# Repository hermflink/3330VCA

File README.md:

# 3330VCA

Kicad project files of a AS3330 based dual VCA. Part of a modular DIY synth project, other modules are available in other repositories. Not entirely compatible with a CEM3330 as this would require a diode to ground on pin 4.

Used the Audio.lib from https://kicad.github.io/symbols/Audio to extend the Kicad library for the AS3330 component.

Designed to work with +/- 15V, not tested for +/- 12V

The PCB is 9.5 x 5.5 cm and has no PCB-mounting of potmeters, switches, jacks; these are all connected by pin header connectors

The PCB  has a fault: the connection between pin 5 and 8 of AS3330 on the backplane should be removed. Instead, pin 5 should be connected to R15/R17 as the schema points out.

Loosely based on http://www.digisound80.co.uk/digisound/modules/80-9_files/80-9_ETI.pdf

R4, C2, R18 and C8 can be safely left out.

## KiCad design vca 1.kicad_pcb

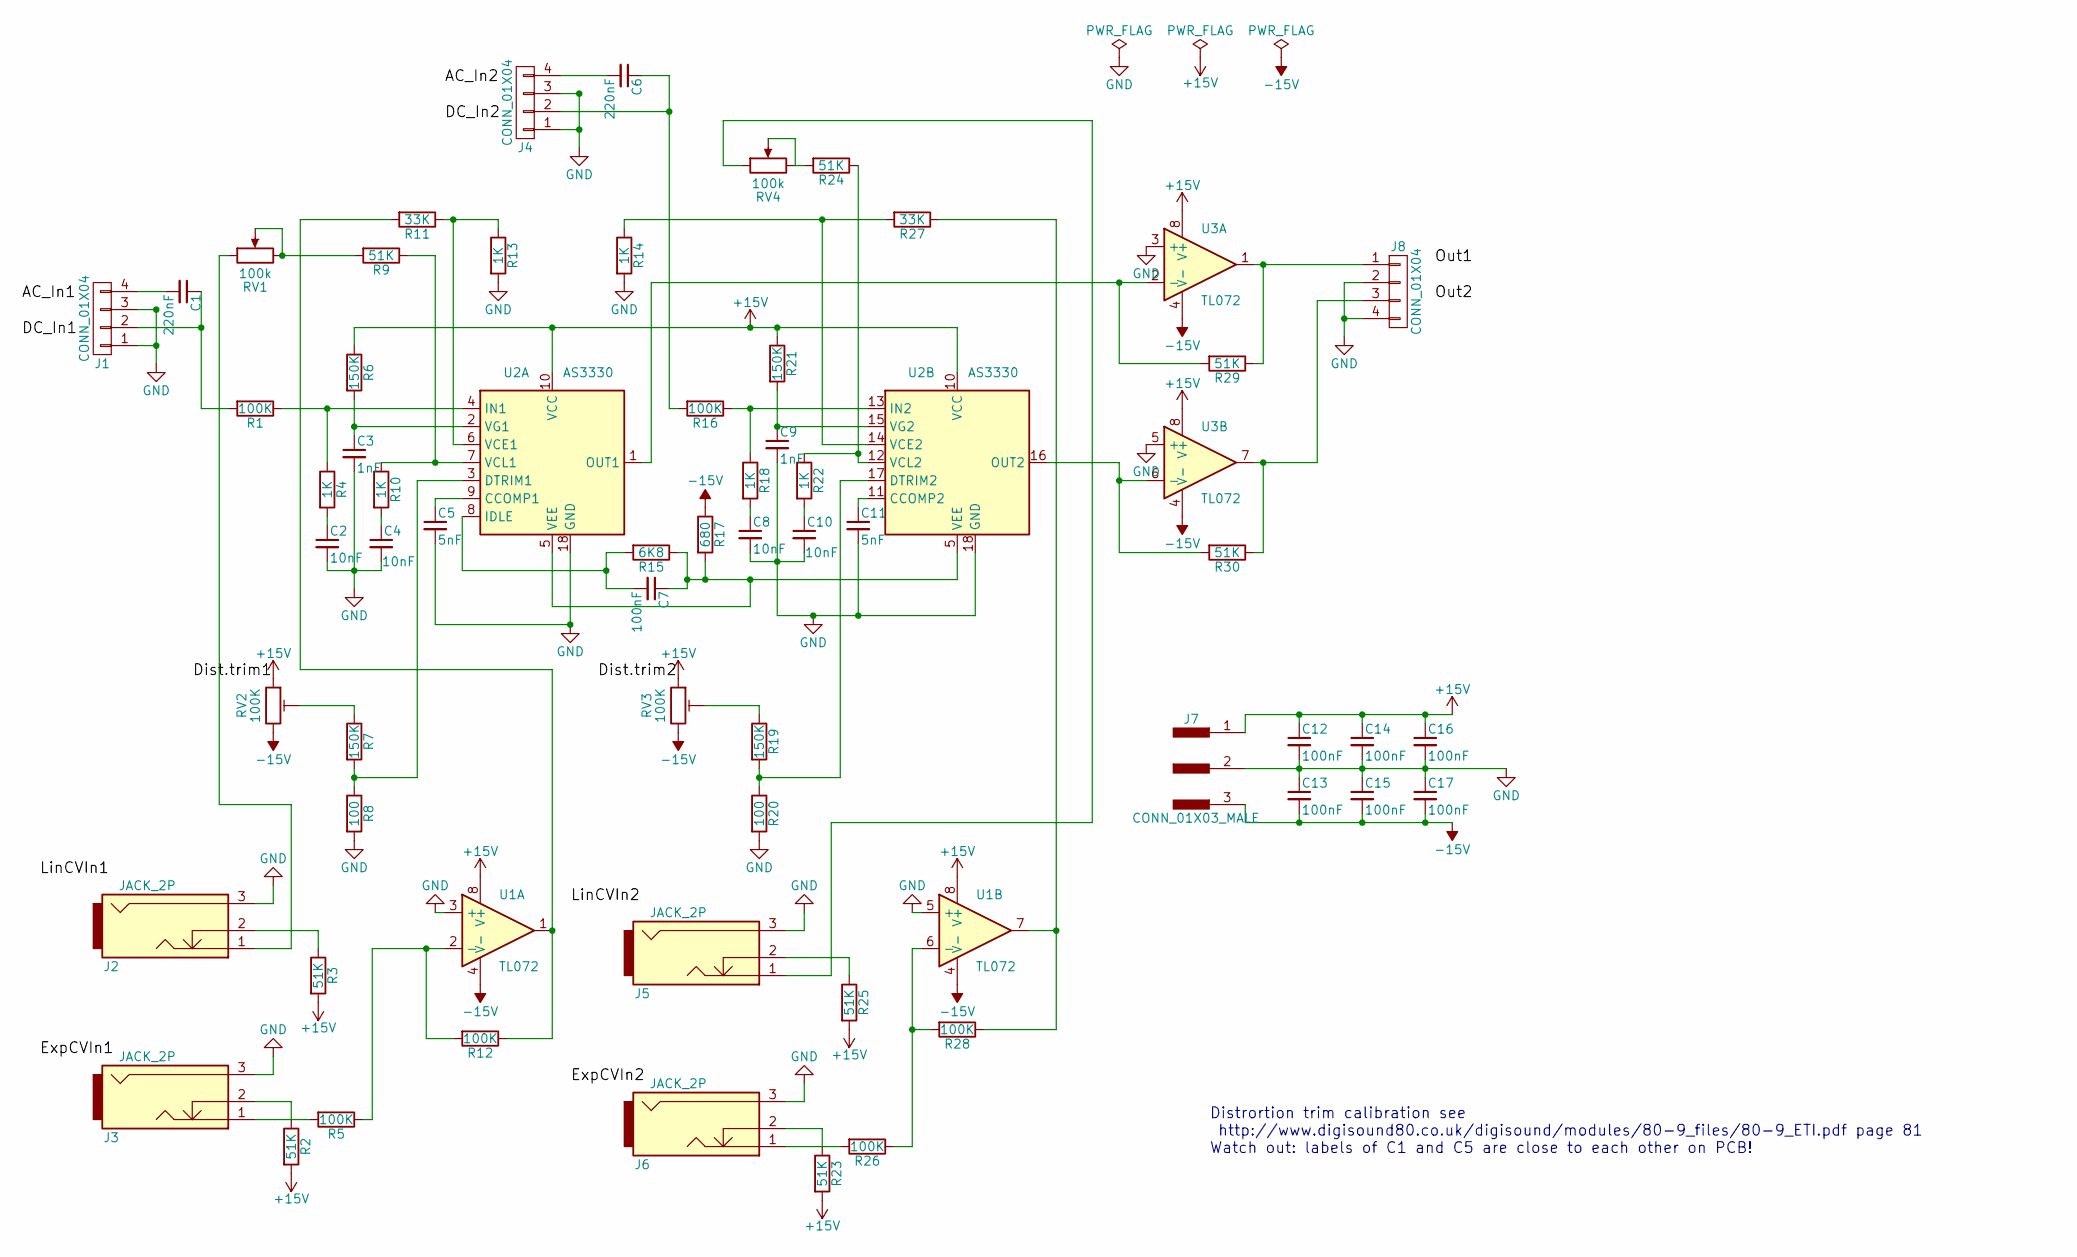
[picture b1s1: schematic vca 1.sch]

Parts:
C1, C6: 220nF; C_Disc_D5.0mm_W2.5mm_P5.00mm
C2, C4, C8, C10: 10nF; C_Disc_D5.0mm_W2.5mm_P5.00mm
C3, C9: 1nF; C_Disc_D5.0mm_W2.5mm_P5.00mm
C5, C11: 5nF; C_Disc_D5.0mm_W2.5mm_P5.00mm
C7, C12, C13, C14, C15, C16, C17: 100nF; C_Disc_D5.0mm_W2.5mm_P5.00mm
J1, J4, J8: CONN_01X04; Pin_Header_Straight_1x04_Pitch2.54mm
J2, J3, J5, J6: JACK_2P; Pin_Header_Straight_1x03_Pitch2.54mm
J7: CONN_01X03_MALE; Pin_Header_Straight_1x03_Pitch2.54mm
R1, R5, R12, R16, R26, R28: 100K; R_Axial_DIN0207_L6.3mm_D2.5mm_P2.54mm_Vertical
R2, R3, R9, R23, R24, R25, R29, R30: 51K; R_Axial_DIN0207_L6.3mm_D2.5mm_P2.54mm_Vertical
R4, R10, R13, R14, R18, R22: 1K; R_Axial_DIN0207_L6.3mm_D2.5mm_P2.54mm_Vertical
R6, R7, R19, R21: 150K; R_Axial_DIN0207_L6.3mm_D2.5mm_P2.54mm_Vertical
R8, R20: 100; R_Axial_DIN0207_L6.3mm_D2.5mm_P2.54mm_Vertical
R11, R27: 33K; R_Axial_DIN0207_L6.3mm_D2.5mm_P2.54mm_Vertical
R15: 6K8; R_Axial_DIN0207_L6.3mm_D2.5mm_P2.54mm_Vertical
R17: 680; R_Axial_DIN0207_L6.3mm_D2.5mm_P2.54mm_Vertical
RV1, RV4: 100k; Pin_Header_Straight_1x03_Pitch2.54mm
RV2, RV3: 100K; Potentiometer_Trimmer_Bourns_3296W
U1, U3: TL072; DIP-8_W7.62mm_Socket_LongPads
U2: AS3330; DIP-18_W7.62mm_Socket_LongPads

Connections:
+15V: C12.1, C14.1, C16.1, J7.1, R2.2, R3.2, R6.1, R21.1, R23.2, R25.2, RV2.1, RV3.1, U1.8 (V+), U2.10 (VCC), U3.8 (V+)
-15V: C13.2, C15.2, C17.2, J7.3, R17.1, RV2.3, RV3.3, U1.4 (V-), U3.4 (V-)
GND: C2.2, C3.2, C4.2, C5.2, C8.2, C9.2, C10.2, C11.2, C12.2, C13.1, C14.2, C15.1, C16.2, C17.1, J1.1, J1.3, J2.3, J3.3, J4.1, J4.3, J5.3, J6.3, J7.2, J8.2, J8.4, R8.2, R13.2, R14.2, R20.2, U1.3 (+), U1.5 (+), U2.18 (GND), U3.3 (+), U3.5 (+)
unnamed: C1.1, J1.2, R1.2
unnamed: C1.2, J1.4
unnamed: C2.1, R4.2
unnamed: C3.1, R6.2, U2.2 (VG1)
unnamed: C4.1, R10.2
unnamed: C5.1, U2.9 (CCOMP1)
unnamed: C6.1, J4.2, R16.2
unnamed: C6.2, J4.4
unnamed: C8.1, R18.2
unnamed: C9.1, R21.2, U2.15 (VG2)
unnamed: C10.1, R22.2
unnamed: C11.1, U2.11 (CCOMP2)
unnamed: J2.1, RV1.1
unnamed: J2.2, R3.1
unnamed: J3.1, R5.2
unnamed: J3.2, R2.1
unnamed: J5.1, RV4.1
unnamed: J5.2, R25.1
unnamed: J6.1, R26.2
unnamed: J6.2, R23.1
unnamed: J8.1, R29.1, U3.1
unnamed: J8.3, R30.1, U3.7
unnamed: R1.1, R4.1, U2.4 (IN1)
unnamed: R7.1, RV2.2
unnamed: R7.2, R8.1, U2.3 (DTRIM1)
unnamed: R9.2, RV1.2, RV1.3
unnamed: R9.1, R10.1, U2.7 (VCL1)
unnamed: R11.1, R13.1, U2.6 (VCE1)
unnamed: R11.2, R12.1, U1.1
unnamed: R5.1, R12.2, U1.2 (-)
unnamed: R14.1, R27.2, U2.14 (VCE2)
unnamed: R16.1, R18.1, U2.13 (IN2)
unnamed: R19.1, RV3.2
unnamed: R19.2, R20.1, U2.17 (DTRIM2)
unnamed: R22.1, R24.1, U2.12 (VCL2)
unnamed: R24.2, RV4.2, RV4.3
unnamed: R26.1, R28.2, U1.6 (-)
unnamed: R27.1, R28.1, U1.7
unnamed: R29.2, U2.1 (OUT1), U3.2 (-)
unnamed: R30.2, U2.16 (OUT2), U3.6 (-)

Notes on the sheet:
Distrortion trim calibration see http://www.digisound80.co.uk/digisound/modules/80-9_files/80-9_ETI.pdf page 81 Watch out: labels of C1 and C5 are close to each other on PCB!

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
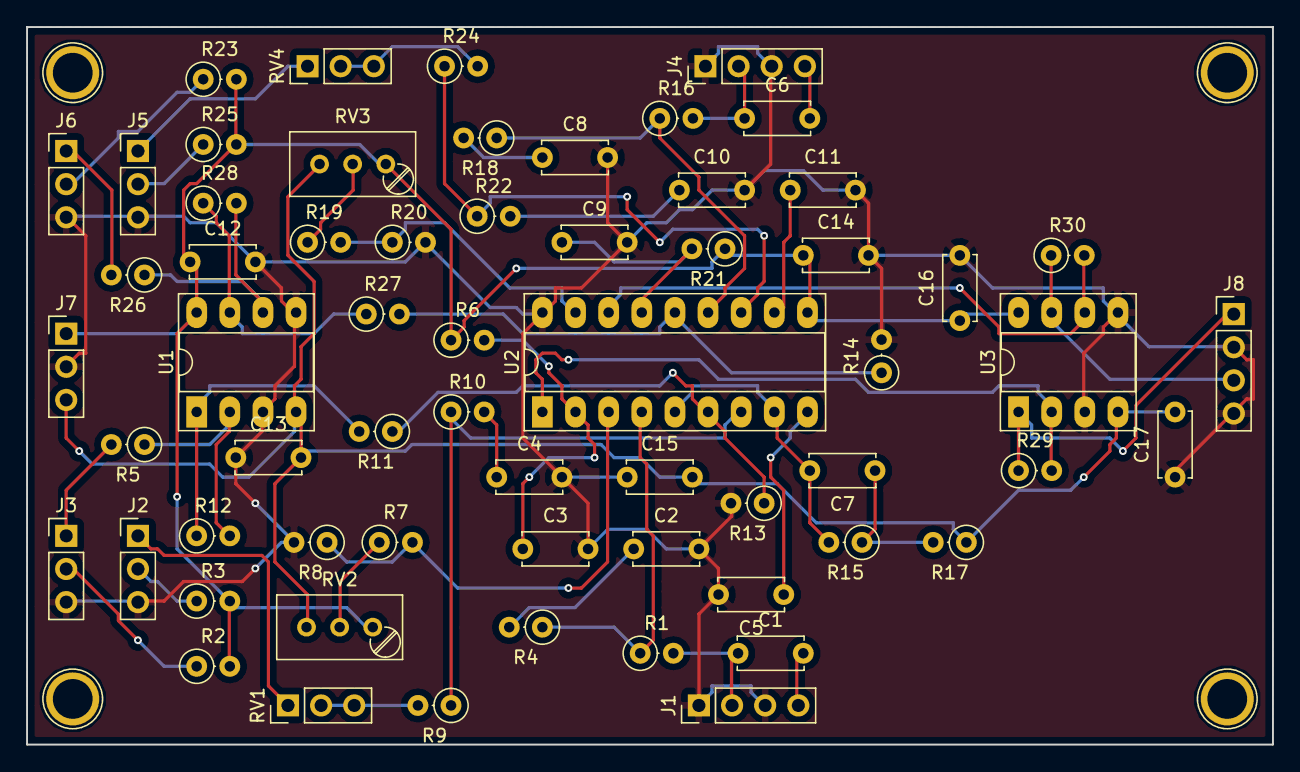
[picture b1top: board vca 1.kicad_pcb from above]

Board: 2 copper layers, 95.5 x 55.0 mm, 62 parts (0 on the bottom side), 45 nets.

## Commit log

2019-11-08 Create LICENSE
